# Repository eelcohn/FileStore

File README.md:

# FileStore
Econet FileStore server and gateway

This project is still work in progress and NOT by any means working!

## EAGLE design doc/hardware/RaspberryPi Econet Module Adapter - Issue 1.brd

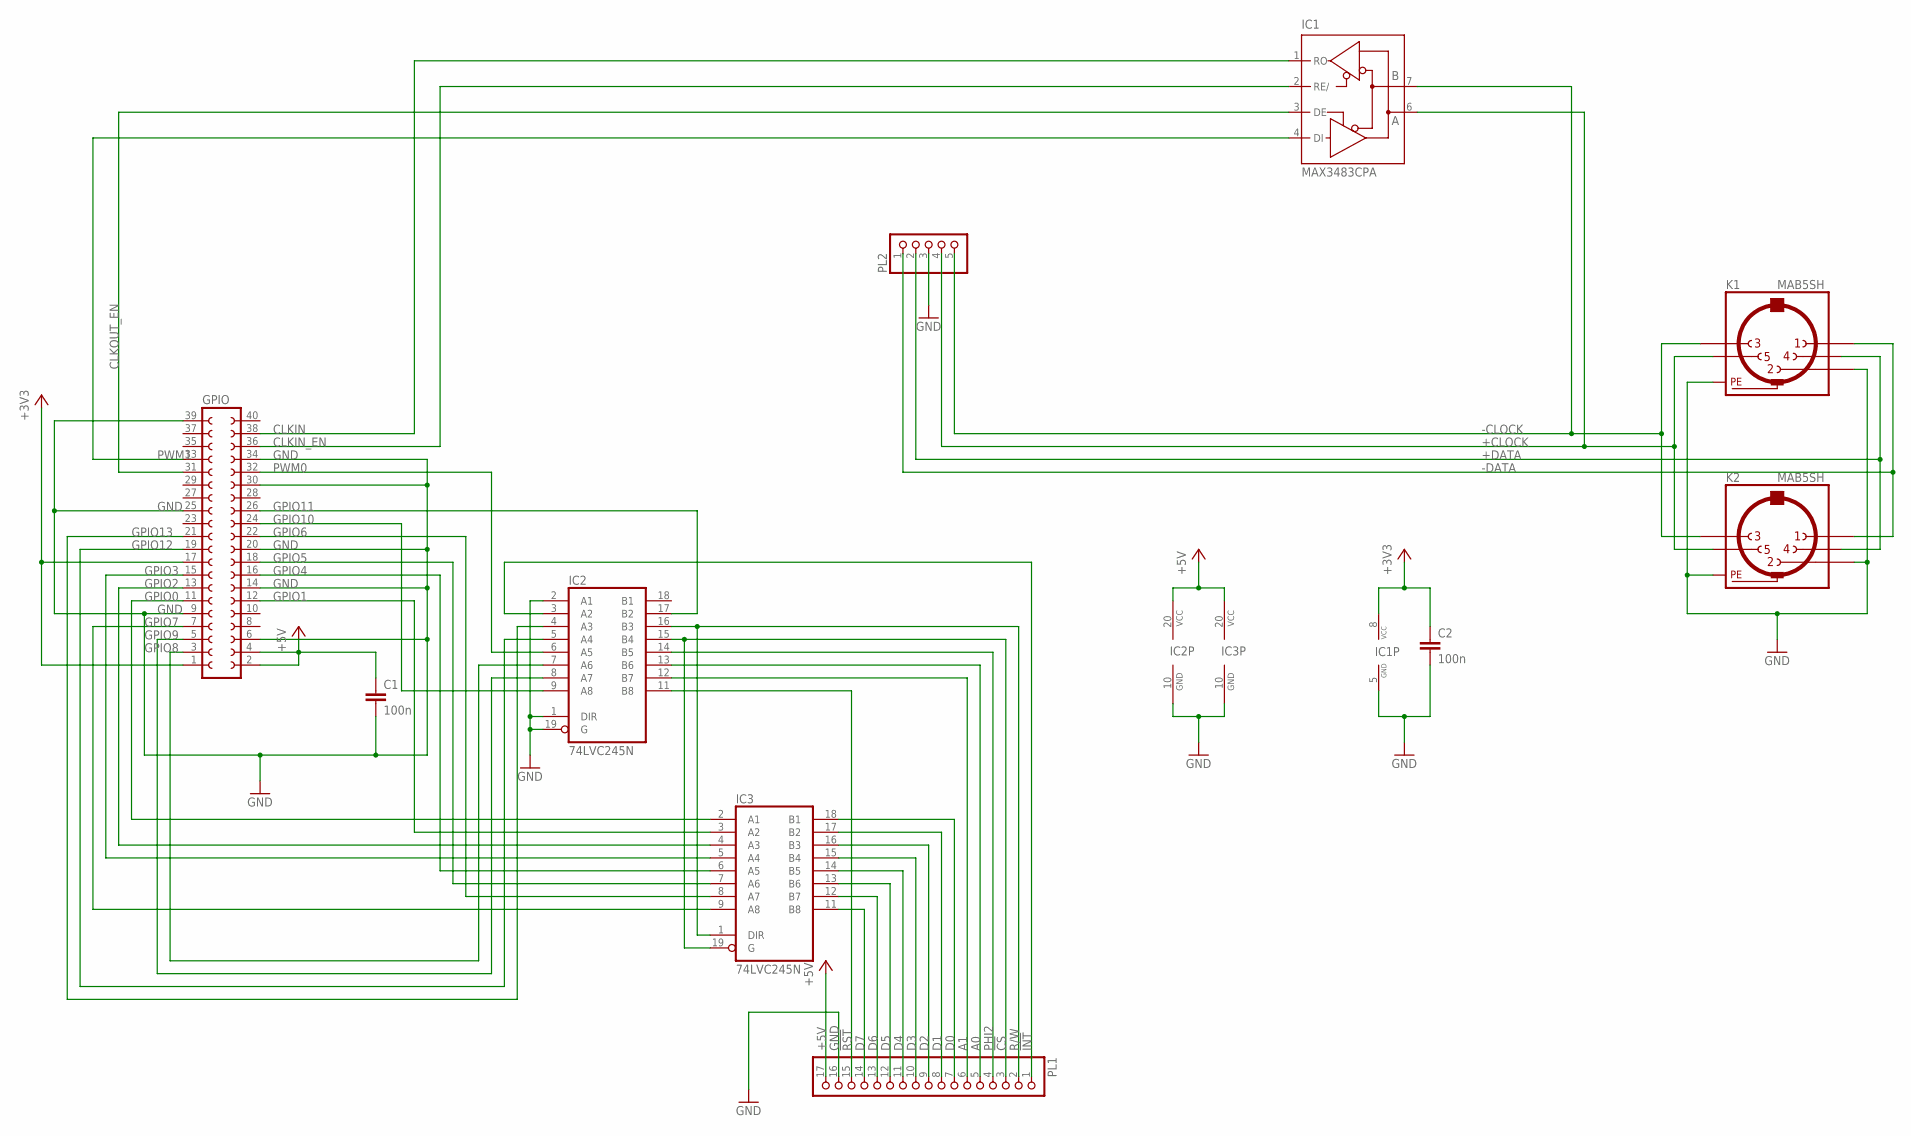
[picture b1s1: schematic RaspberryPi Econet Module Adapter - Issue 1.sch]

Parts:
C1, C2: 100n; C050-025X075
GPIO: FE20-2
IC1: MAX3483CPA; DIL08
IC2, IC3: 74LVC245N; DIL20
K1, K2: MAB5SH
PL1: PINHD-1X17; 1X17
PL2: PINHD-1X5; 1X05

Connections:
!CS: IC2.15 (B4), IC3.19 (G), PL1.3
!INT: IC2.3 (A2), PL1.1
!RST: IC2.11 (B8), PL1.15
+3V3: C2.1, GPIO.1, GPIO.17, IC1.8 (VCC)
+5V: C1.1, GPIO.2, GPIO.4, IC2.20 (VCC), IC3.20 (VCC), PL1.17
+CLOCK: IC1.6 (A), K1.5, K2.5, PL2.4
+DATA: K1.4, K2.4, PL2.2
-CLOCK: IC1.7 (B), K1.3, K2.3, PL2.5
-DATA: K1.1, K2.1, PL2.1
A0: IC2.13 (B6), PL1.5
A1: IC2.12 (B7), PL1.6
CLKIN: GPIO.38, IC1.1 (RO)
CLKIN_EN: GPIO.36, IC1.2 (RE/)
CLKOUT_EN: GPIO.31, IC1.3 (DE)
D0: IC3.18 (B1), PL1.7
D1: IC3.17 (B2), PL1.8
D2: IC3.16 (B3), PL1.9
D3: IC3.15 (B4), PL1.10
D4: IC3.14 (B5), PL1.11
D5: IC3.13 (B6), PL1.12
D6: IC3.12 (B7), PL1.13
D7: IC3.11 (B8), PL1.14
GND: C1.2, C2.2, GPIO.6, GPIO.9, GPIO.14, GPIO.20, GPIO.25, GPIO.30, GPIO.34, GPIO.39, IC1.5 (GND), IC2.1 (DIR), IC2.2 (A1), IC2.10 (GND), IC2.19 (G), IC3.10 (GND), K1.2, K1.PE, K1.PE@ (PE), K2.2, K2.PE, K2.PE@ (PE), PL1.16, PL2.3
GPIO0: GPIO.11, IC3.2 (A1)
GPIO1: GPIO.12, IC3.3 (A2)
GPIO2: GPIO.13, IC3.4 (A3)
GPIO3: GPIO.15, IC3.5 (A4)
GPIO4: GPIO.16, IC3.6 (A5)
GPIO5: GPIO.18, IC3.7 (A6)
GPIO6: GPIO.22, IC3.8 (A7)
GPIO7: GPIO.7, IC3.9 (A8)
GPIO8: GPIO.3, IC2.7 (A6)
GPIO9: GPIO.5, IC2.8 (A7)
GPIO10: GPIO.24, IC2.9 (A8)
GPIO11: GPIO.26, IC2.17 (B2)
GPIO12: GPIO.19, IC2.5 (A4)
GPIO13: GPIO.21, IC2.4 (A3)
PHI2: IC2.14 (B5), PL1.4
PWM0: GPIO.32, IC2.6 (A5)
PWM1: GPIO.33, IC1.4 (DI)
R/W: IC2.16 (B3), IC3.1 (DIR), PL1.2

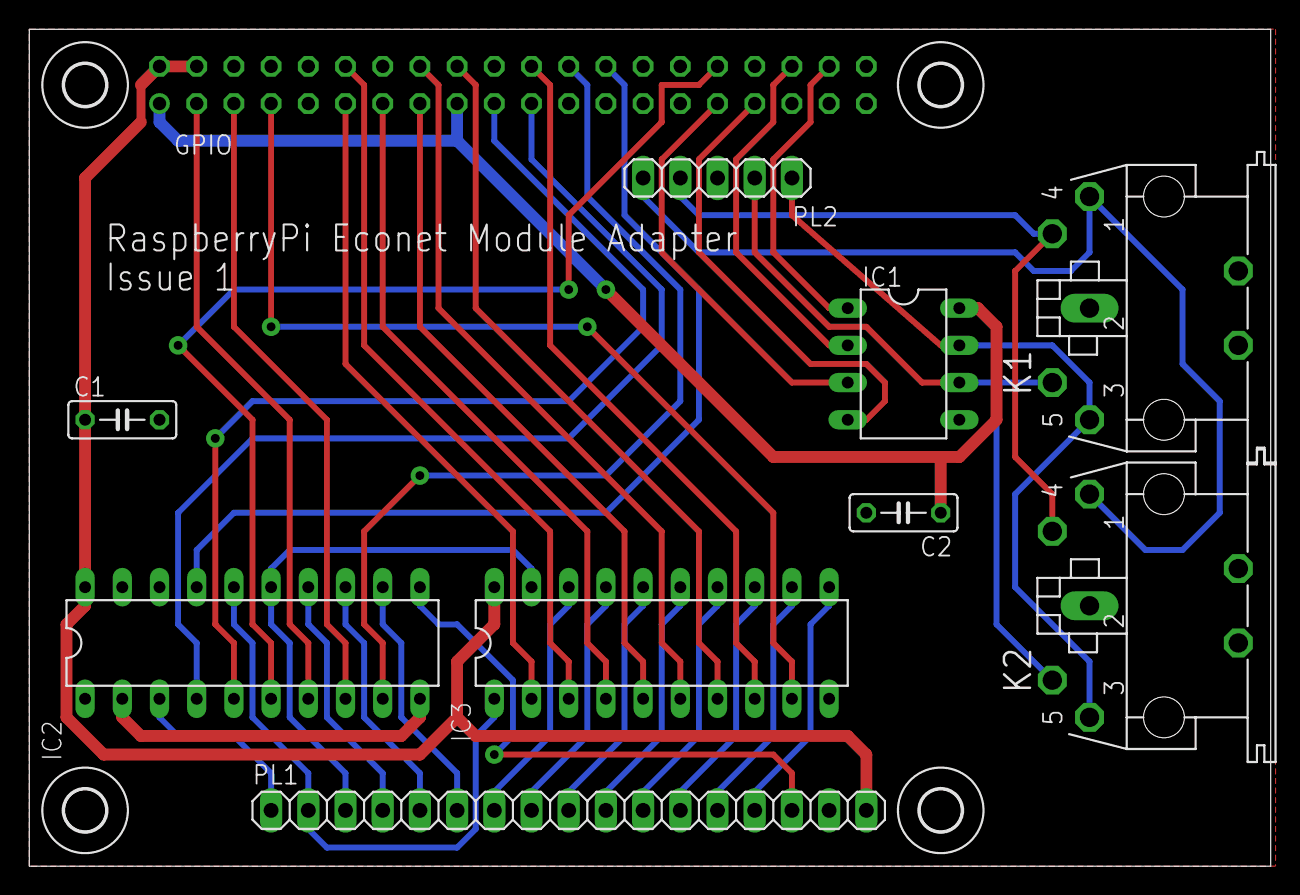
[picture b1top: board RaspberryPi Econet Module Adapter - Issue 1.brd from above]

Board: 2 copper layers, 84.8 x 57.1 mm, 14 parts (1 on the bottom side), 41 nets.

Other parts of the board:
U$1, U$2, U$3, U$4: 2,8

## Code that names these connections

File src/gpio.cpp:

/* gpio.cpp
 * Low-level driver for the Econet module interface,
 * connected to the Raspberry Pi GPIO
 *
 * (c) Eelco Huininga 2017-2018
 */

#include "gpio.h"
#include "configuration.h"
#include <pigpio.h>

using namespace std;




namespace gpio {
	bool clockStarted;



	int initializeGPIO(void) {
		return (gpioInitialise());	// Initialize the pigpio library
	}

	int stopGPIO(void) {
		gpioTerminate();		// Terminate the pigpio library
		return (0);
	}

	int resetADLC(void) {
		// Set all pins to their default state
		gpioSetMode(ADLC_D0, PI_INPUT);
		gpioSetMode(ADLC_D1, PI_INPUT);
		gpioSetMode(ADLC_D2, PI_INPUT);
		gpioSetMode(ADLC_D3, PI_INPUT);
		gpioSetMode(ADLC_D4, PI_INPUT);
		gpioSetMode(ADLC_D5, PI_INPUT);
		gpioSetMode(ADLC_D6, PI_INPUT);
		gpioSetMode(ADLC_D7, PI_INPUT);
		gpioSetMode(ADLC_A0, PI_OUTPUT);
		gpioSetMode(ADLC_A1, PI_OUTPUT);
		gpioSetMode(ADLC_CS, PI_OUTPUT);
		gpioSetMode(ADLC_RW, PI_OUTPUT);
		gpioSetMode(ADLC_RST, PI_INPUT);
		gpioSetMode(ADLC_IRQ, PI_INPUT);

		gpioSetMode(CLKIN, PI_INPUT);
		gpioSetMode(CLKIN_EN, PI_OUTPUT);
		gpioSetMode(CLKOUT, PI_OUTPUT);
		gpioSetMode(CLKOUT_EN, PI_OUTPUT);

		// Initialize bus signals
		gpioWrite (ADLC_RST, PI_HIGH);			// Don't reset the beast just yet
		gpioWrite (ADLC_CS, PI_HIGH);			// Disable ADLC for now
		gpioWrite (ADLC_RW, PI_HIGH);			// Read
		gpioWrite (ADLC_A0, PI_LOW);			// Select register 0
		gpioWrite (ADLC_A1, PI_LOW);			// 

		gpioWrite (CLKIN_EN, PI_LOW);
		gpioWrite (CLKOUT, PI_LOW);
		gpioWrite (CLKOUT_EN, PI_LOW);

		// Start Phi2 clock (min=0.5us max=10us for a 68B54 according to the datasheet)
		gpioHardwarePWM(ADLC_PHI2, 1000000, 500000);	// Set phi2 to 1MHz, 50% duty cycle

		// Set up IRQ handler
//		gpioSetISRFunc(ADLC_IRQ, FALLING_EDGE, ADLC_INTERRUPT_TIMEOUT, &gpio::irqHandler);

		// Pulse RST low to reset the ADLC
		gpioWrite(ADLC_RST, PI_LOW);
		gpioSleep(PI_TIME_RELATIVE, 0, ADLC_RESET_PULSEWIDTH);
		gpioWrite(ADLC_RST, PI_HIGH);

		gpio::initializeADLC();
		return (0);
	}

	int powerDownADLC(void) {
		// Pulse RST low to reset the ADLC
		gpioWrite(ADLC_RST, PI_LOW);
		gpioSleep(PI_TIME_RELATIVE, 0, ADLC_RESET_PULSEWIDTH);
		gpioWrite(ADLC_RST, PI_HIGH);

		// Stop Phi2 clock
		gpioHardwarePWM(ADLC_PHI2, 0, 0);

		// Set all pins to their default state
		gpioSetMode(ADLC_D0, PI_INPUT);
		gpioSetMode(ADLC_D1, PI_INPUT);
		gpioSetMode(ADLC_D2, PI_INPUT);
		gpioSetMode(ADLC_D3, PI_INPUT);
		gpioSetMode(ADLC_D4, PI_INPUT);
		gpioSetMode(ADLC_D5, PI_INPUT);
		gpioSetMode(ADLC_D6, PI_INPUT);
		gpioSetMode(ADLC_D7, PI_INPUT);
		gpioSetMode(ADLC_A0, PI_INPUT);
		gpioSetMode(ADLC_A1, PI_INPUT);
		gpioSetMode(ADLC_CS, PI_INPUT);
		gpioSetMode(ADLC_RW, PI_INPUT);
		gpioSetMode(ADLC_RST, PI_INPUT);
		gpioSetMode(ADLC_IRQ, PI_INPUT);

		gpioSetMode(CLKIN, PI_INPUT);
		gpioSetMode(CLKIN_EN, PI_INPUT);
		gpioSetMode(CLKOUT, PI_INPUT);
		gpioSetMode(CLKOUT_EN, PI_INPUT);

		return (0);
	}

	// Initialize ADLC registers
	void initializeADLC(void) {
		gpio::writeRegister(0, 0xC1);
		gpio::writeRegister(3, 0x1E);
		gpio::writeRegister(1, 0x00);
		gpio::writeRegister(0, 0x82);
		gpio::writeRegister(1, 0x67);
	}

	// Poll the ADLC until an IRQ occurs
	void waitForADLCInterrupt(void) {
		bool interrupt;

		interrupt = false;
		while (interrupt == false)
			interrupt = (gpio::readRegister(0) && 0x80);
	}

	// ADLC hardware IRQ handler
	void irqHandler(void) {
	}

	unsigned char readRegister(unsigned char reg) {
		unsigned char result = 0x00;

		gpioWrite(ADLC_RW, PI_HIGH);
		if (reg & 0x01)
			gpioWrite(ADLC_A0, PI_HIGH);
		else
			gpioWrite(ADLC_A0, PI_LOW);
		if (reg & 0x02)
			gpioWrite(ADLC_A1, PI_HIGH);
		else
			gpioWrite(ADLC_A1, PI_LOW);
		gpioWrite(ADLC_CS, PI_LOW);
		gpioSleep(PI_TIME_RELATIVE, 0, ADLC_BUS_SETTLE_TIME);

		if (gpioRead(ADLC_D0))
			result |= 0x01;
		if (gpioRead(ADLC_D1))
			result |= 0x02;
		if (gpioRead(ADLC_D2))
			result |= 0x04;
		if (gpioRead(ADLC_D3))
			result |= 0x08;
		if (gpioRead(ADLC_D4))
			result |= 0x10;
		if (gpioRead(ADLC_D5))
			result |= 0x20;
		if (gpioRead(ADLC_D6))
			result |= 0x40;
		if (gpioRead(ADLC_D7))
			result |= 0x80;
		gpioWrite(ADLC_CS, PI_HIGH);
		gpioSleep(PI_TIME_RELATIVE, 0, ADLC_BUS_SETTLE_TIME);

		return (result);
	}

	void writeRegister(unsigned char reg, unsigned char value) {
		gpioWrite(ADLC_RW, PI_LOW);

		// Set address bus
		if (reg & 0x01)
			gpioWrite(ADLC_A0, PI_HIGH);
		else
			gpioWrite(ADLC_A0, PI_LOW);
		if (reg & 0x02)
			gpioWrite(ADLC_A1, PI_HIGH);
		else
			gpioWrite(ADLC_A1, PI_LOW);

		// Set databus
		if (value & 0x01)
			gpioWrite(ADLC_D0, PI_HIGH);
		else
			gpioWrite(ADLC_D0, PI_LOW);
		if (value & 0x02)
			gpioWrite(ADLC_D1, PI_HIGH);
		else
			gpioWrite(ADLC_D1, PI_LOW);
		if (value & 0x04)
			gpioWrite(ADLC_D2, PI_HIGH);
		else
			gpioWrite(ADLC_D2, PI_LOW);
		if (value & 0x08)
			gpioWrite(ADLC_D3, PI_HIGH);
		else
			gpioWrite(ADLC_D3, PI_LOW);
		if (value & 0x10)
			gpioWrite(ADLC_D4, PI_HIGH);
		else
			gpioWrite(ADLC_D4, PI_LOW);
		if (value & 0x20)
			gpioWrite(ADLC_D5, PI_HIGH);
		else
			gpioWrite(ADLC_D5, PI_LOW);
		if (value & 0x40)
			gpioWrite(ADLC_D6, PI_HIGH);
		else
			gpioWrite(ADLC_D6, PI_LOW);
		if (value & 0x80)
			gpioWrite(ADLC_D7, PI_HIGH);
		else
			gpioWrite(ADLC_D7, PI_LOW);

		gpioWrite(ADLC_CS, PI_LOW);
		gpioSleep(PI_TIME_RELATIVE, 0, ADLC_BUS_SETTLE_TIME);
		gpioWrite(ADLC_CS, PI_HIGH);
		gpioSleep(PI_TIME_RELATIVE, 0, ADLC_BUS_SETTLE_TIME);
	}
	// Send an Econet packet over the Econet interface
	int transmitData(econet::Frame *frame, unsigned int length) {
		unsigned int i = 0;

		gpio::writeRegister(1, 0xE7);
		gpio::writeRegister(0, 0x44);
		do {
			gpio::waitForADLCInterrupt();
//			gpio::writeRegister(2, (unsigned char *) &frame[i);
			i++;
		} while (i < length);
		gpio::writeRegister(1, 0x3F);
		gpio::waitForADLCInterrupt();

		return (0);
	}

	// Receive an Econet packet over the Econet interface
	int receiveData(econet::Frame *frame) {
		int result, i = 0;
		unsigned char status;

		frame->status = 0x00;

		gpio::writeRegister(0, 0x82);
		if (gpio::readRegister(1) && 0x01) {
			while (!(gpio::readRegister(1) && 0x80))
				frame->data[i++] = gpio::readRegister(2);

			gpio::writeRegister(0, 0x00);
			gpio::writeRegister(1, 0x84);
			status = gpio::readRegister(1);
			if (status && 0x02) {
				if (status && 0x80)
					status = gpio::readRegister(2);	// Fetch last byte in receive buffer
				if (frame->data[3] == 0)	// Replace local network (0) with our real network number
					frame->data[3] = configuration::econet_network;
				result = i - 1;
			} else
				return(-1);	// No valid frame found
		} else
			return(-2);
		return (result);
	}

	// SWI &4001A: Econet_NetworkState
	bool networkState(void) {
		// Return the DCD bit in ADLC status register 2
		return (gpio::readRegister(1) && 0x20);
	}

	int setClockSpeed(unsigned int clockSpeed, unsigned int dutyCycle) {
		if (clockSpeed > MAX_CLOCKSPEED)
			return (-1);
		else
			configuration::clockspeed = clockSpeed;

		if (dutyCycle > MAX_DUTYCYCLE)
			return (-2);
		else
			configuration::dutycycle = dutyCycle;

		if (gpio::clockStarted == true)
			gpio::startClock();

		return (0);
	}

	int getClockSpeed(void) {
		return (-1);
	}

	void startClock(void) {
		gpioHardwarePWM(CLKOUT, configuration::clockspeed, (configuration::dutycycle * 10000));
	}

	// Stop Econet clock
	void stopClock(void) {
		gpioHardwarePWM(CLKOUT, 0, 0);
	}
}

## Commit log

2018-06-02 Updated Makefile with client recipe and generating the certificates
2018-06-02 Removed some temp files
2018-06-02 Updated code
2018-06-02 Added schema and PCB for Issue 1 of the hardware
2018-06-04 Updated Makefile & code cleanup
2018-06-11 Pushed several updates
2018-06-11 Bugfixes
2018-06-13 Fixed some bugs when compiling on RaspberryPi hardware
2018-06-13 Updates and bugfixes
2018-06-13 Bugfixes and updates
2018-06-13 Moved from WiringPi library to pigpio library
2018-06-13 Replaced wiringPi library with pigpio library
2018-06-14 Re-arranged some code
2018-06-14 Added preliminary clock frequency counter
2018-06-18 Added preliminary IPv6 support
2018-06-18 Renamed functions
2018-06-19 Added udp test client
2018-06-20 Added support for OpenSSL < v1.1.0
2018-06-20 Prelimiary IPv6 support
2018-06-20 Added OpenSSL debug scripts
2018-06-20 Added dtls example
2018-06-20 Preliminary IPv6 listener
2018-06-21 Renamed ethernet.* to aun.*
2018-06-25 Set Phi2 to 2MHz; updated getClockSpeed()
2018-06-25 Updated Econet::Frame with union
2018-06-26 Bugfix: Set ADLC_RST line as output
2018-06-27 Moved all CLI commands to cli.cpp
2018-07-03 Replaced strcpy with strlcpy
2018-07-03 Replaced strcpy() with strlcpy()
2019-01-09 Updated FileStore source code
2019-01-10 Updated filesystem-handlers
2019-01-13 Updated submodules
2019-09-01 Removed double -g flag
2019-09-03 Moved linux code to ./platforms/linux/
2019-09-03 Create !Users
2019-09-04 Fixed error messages
2020-01-06 Update build
2020-01-06 netfs::attribtostr() returns size of attrib string
